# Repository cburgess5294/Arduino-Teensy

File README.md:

# Arduino-Teensy
Repository for files related to the Arduino-Teensy v4

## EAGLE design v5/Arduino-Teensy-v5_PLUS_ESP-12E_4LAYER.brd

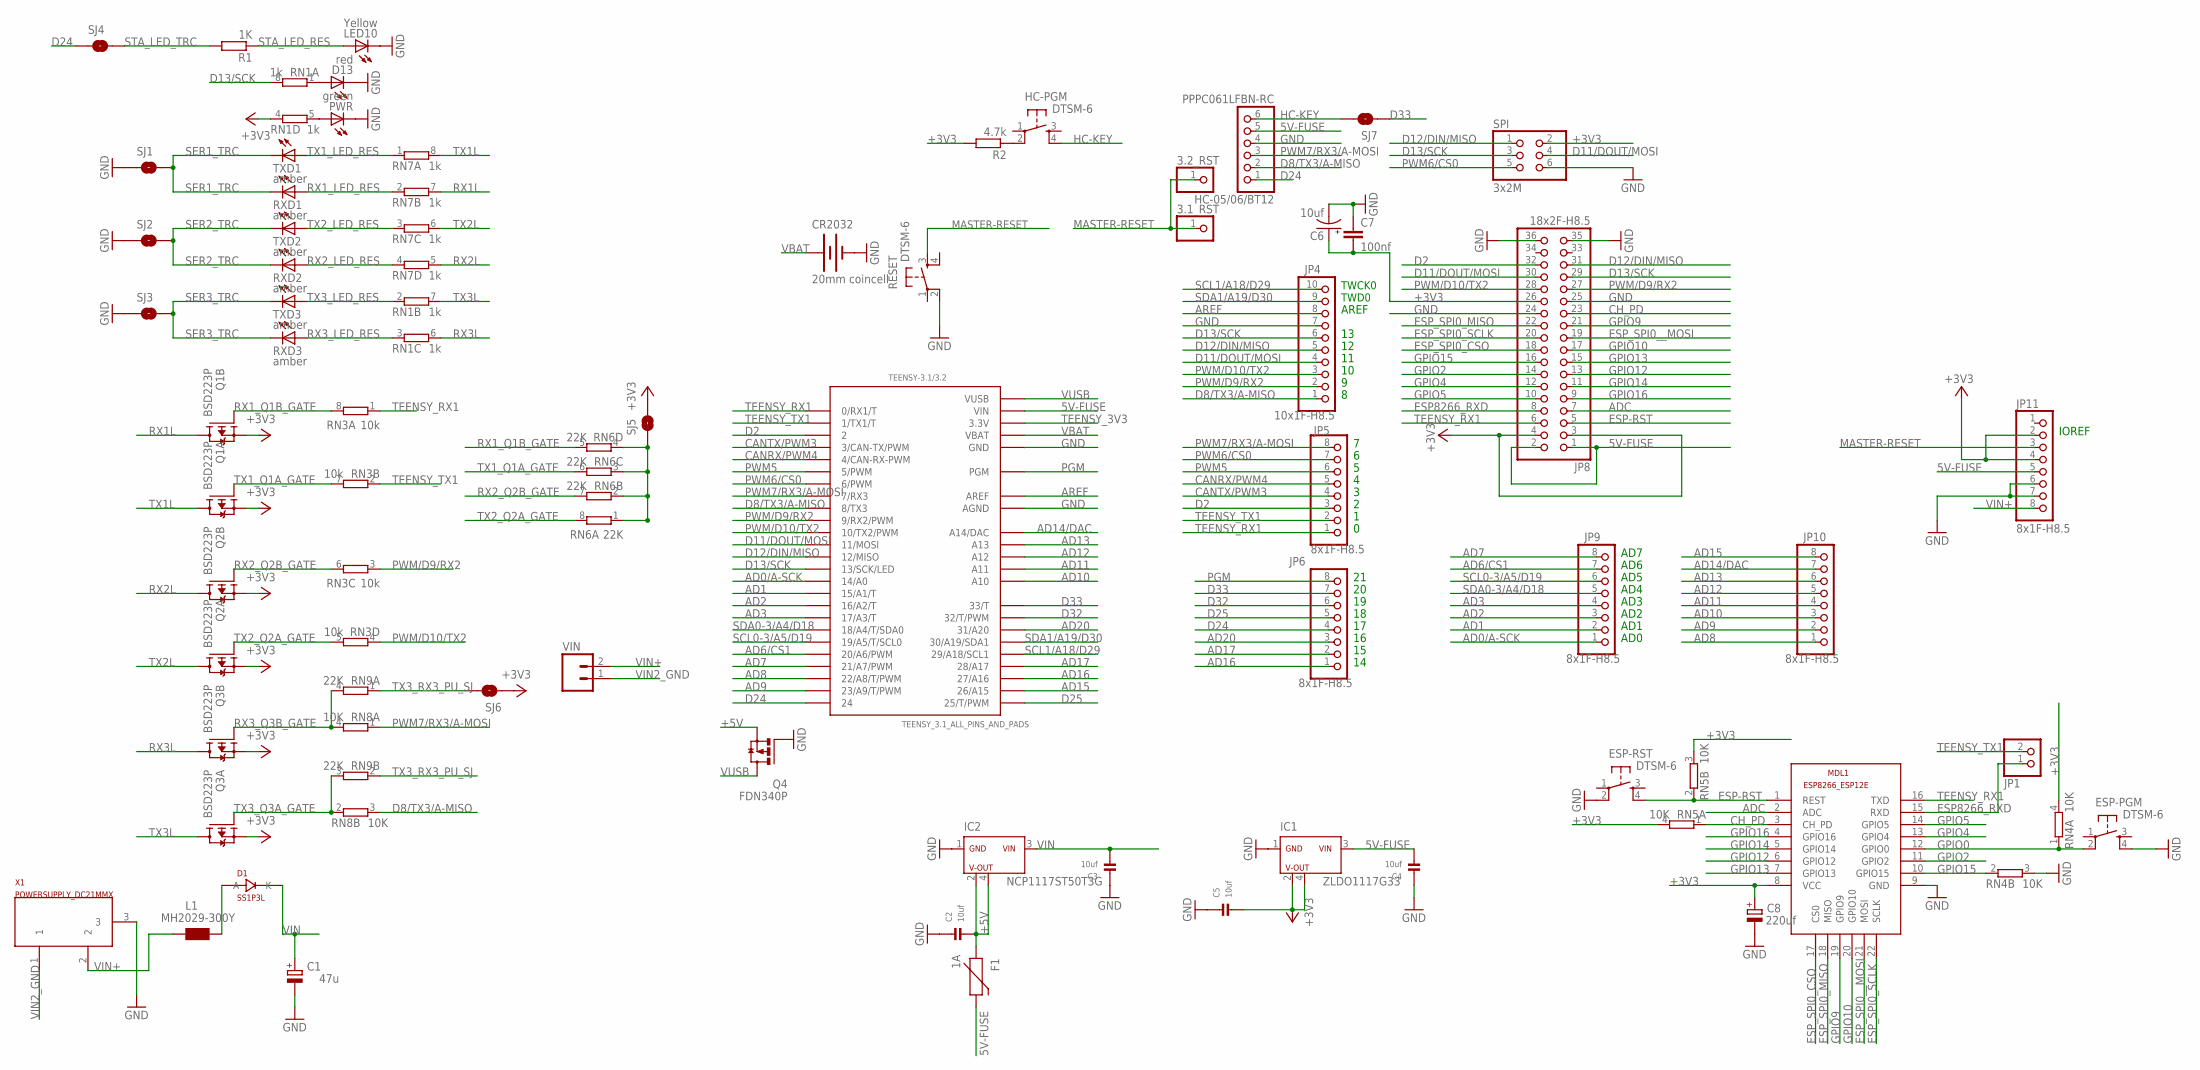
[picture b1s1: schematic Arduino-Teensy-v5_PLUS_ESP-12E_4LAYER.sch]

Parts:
3.1_RST, 3.2_RST: PINHD-1X1CB; 1X01-CLEANBIG
C1: 47u; PANASONIC_D
C2, C3, C4, C5: 10uf; 0805
C6: 10uf; A/3216-18R
C7: 100nf; C0603-ROUND
C8: 220uf; SMC_B
CR2032: 20mm coincell; BATTCON_20MM_4LEGS
D1: SS1P3L; DO220AAL
D13: red; CHIPLED_0805
ESP-PGM: DTSM-6
ESP-RST: DTSM-6
F1: 1A; PTC-1206
HC-05/06/BT12: PPPC061LFBN-RC; 1X06
HC-PGM: DTSM-6
IC1: ZLDO1117G33; SOT223
IC2: NCP1117ST50T3G; SOT223
JP1: PINHD-1X2; 1X02
JP4: 10x1F-H8.5; 1X10
JP5, JP6, JP9, JP10, JP11: 8x1F-H8.5; 1X08
JP8: 18x2F-H8.5; 2X18
L1: MH2029-300Y; 0805
LED10: Yellow; CHIPLED_0805
MDL1: ESP8266-12E); ESP8266-ESP12E
PWR: green; CHIPLED_0805
Q1, Q2, Q3: BSD223P; SOT363_INFINEON
Q4: FDN340P; SUPER-SOT3
R1: 1K; R0603
R2: 4.7k; R0603
RESET: DTSM-6
RN1, RN7: 1k; CAT16
RN3: 10k; CAT16
RN4, RN5, RN8: 10K; EXB34V
RN6: 22K; CAT16
RN9: 22K; EXB34V
RXD1, RXD2, RXD3: amber; CHIPLED_0805
SJ1, SJ2, SJ3, SJ4, SJ5, SJ6, SJ7: SOLDERJUMPERTRACE; SJ_2S-TRACE
SPI: 3x2M; 2X03
TEENSY-3.1/3.2: TEENSY_3.1_ALL_PINS_AND_PADS; TEENSY3_ALL_PINS_&_PADS
TXD1, TXD2, TXD3: amber; CHIPLED_0805
VIN: M02LOCK_LONGPADS; 1X02_LOCK_LONGPADS
X1: POWERSUPPLY_DC21MMX; POWERSUPPLY_DC-21MM

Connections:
5V-FUSE: C4.2, F1.2, HC-05/06/BT12.5, IC1.3 (VIN), JP8.1, JP8.2, JP11.5, TEENSY-3.1/3.2.VIN
+3V3: C5.2, C6.+, C7.2, C8.+, IC1.2 (VOUT), IC1.4 (VOUT), JP8.3, JP8.4, JP8.26, JP11.2, JP11.4, MDL1.8 (VCC), Q1.1 (S), Q1.4 (S), Q2.1 (S), Q2.4 (S), Q3.1 (S), Q3.4 (S), R2.2, RN1.4 (1), RN4.4 (2), RN5.3 (2), RN5.4 (2), SJ5.2, SJ6.1, SPI.2
+5V: C2.2, F1.1, IC2.2 (VOUT), IC2.4 (VOUT), Q4.2 (S)
AD0/A-SCK: JP9.1, TEENSY-3.1/3.2.14/A0
AD1: JP9.2, TEENSY-3.1/3.2.15/A1 (15/A1/T)
AD2: JP9.3, TEENSY-3.1/3.2.16/A2 (16/A2/T)
AD3: JP9.4, TEENSY-3.1/3.2.17/A3 (17/A3/T)
AD6/CS1: JP9.7, TEENSY-3.1/3.2.20/A6 (20/A6/PWM)
AD7: JP9.8, TEENSY-3.1/3.2.21/A7 (21/A7/PWM)
AD8: JP10.1, TEENSY-3.1/3.2.22/A8 (22/A8/T/PWM)
AD9: JP10.2, TEENSY-3.1/3.2.23/A9 (23/A9/T/PWM)
AD10: JP10.3, TEENSY-3.1/3.2.A10
AD11: JP10.4, TEENSY-3.1/3.2.A11
AD12: JP10.5, TEENSY-3.1/3.2.A12
AD13: JP10.6, TEENSY-3.1/3.2.A13
AD14/DAC: JP10.7, TEENSY-3.1/3.2.RESET/DAC (A14/DAC)
AD15: JP10.8, TEENSY-3.1/3.2.26 (26/A15)
AD16: JP6.1, TEENSY-3.1/3.2.27 (27/A16)
AD17: JP6.2, TEENSY-3.1/3.2.28 (28/A17)
AD20: JP6.3, TEENSY-3.1/3.2.31 (31/A20)
ADC: JP8.7, MDL1.2 (ADC)
AREF: JP4.8, TEENSY-3.1/3.2.AREF
CANRX/PWM4: JP5.5, TEENSY-3.1/3.2.4 (4/CAN-RX-PWM)
CANTX/PWM3: JP5.4, TEENSY-3.1/3.2.3 (3/CAN-TX/PWM)
CH_PD: JP8.23, MDL1.3 (CH_PD), RN5.1
D2: JP5.3, JP8.32, TEENSY-3.1/3.2.2
D8/TX3/A-MISO: HC-05/06/BT12.2, JP4.1, RN8.3 (2), TEENSY-3.1/3.2.8 (8/TX3)
D11/DOUT/MOSI: JP4.4, JP8.30, SPI.4, TEENSY-3.1/3.2.11 (11/MOSI)
D12/DIN/MISO: JP4.5, JP8.31, SPI.1, TEENSY-3.1/3.2.12 (12/MISO)
D13/SCK: JP4.6, JP8.29, RN1.8 (2), SPI.3, TEENSY-3.1/3.2.13 (13/SCK/LED)
D24: HC-05/06/BT12.1, JP6.4, SJ4.1, TEENSY-3.1/3.2.24
D25: JP6.5, TEENSY-3.1/3.2.25 (25/T/PWM)
D32: JP6.6, TEENSY-3.1/3.2.32 (32/T/PWM)
D33: JP6.7, SJ7.2, TEENSY-3.1/3.2.33 (33/T)
ESP8266_RXD: JP1.1, JP8.8, MDL1.15 (RXD)
ESP-RST: ESP-RST.4, JP8.5, MDL1.1 (REST), RN5.2 (1)
ESP_SPI0_CSO: JP8.18, MDL1.17 (CS0)
ESP_SPI0_MISO: JP8.22, MDL1.18 (MISO)
ESP_SPI0_SCLK: JP8.20, MDL1.22 (SCLK)
ESP_SPI0__MOSI: JP8.19, MDL1.21 (MOSI)
GND: C1.-, C2.1, C3.1, C4.1, C5.1, C6.-, C7.1, C8.-, CR2032.NEGATIVE (-), D13.C, ESP-PGM.4, ESP-RST.2, HC-05/06/BT12.4, IC1.1 (GND), IC2.1 (GND), JP4.7, JP8.24, JP8.25, JP8.35, JP8.36, JP11.6, JP11.7, LED10.C, MDL1.9 (GND), PWR.C, Q4.1 (G), RESET.2, RN4.3 (2), SJ1.1, SJ2.1, SJ3.1, SPI.6, TEENSY-3.1/3.2.AGND, TEENSY-3.1/3.2.GND, TEENSY-3.1/3.2.GND1 (GND), TEENSY-3.1/3.2.GND2 (GND), X1.3
GPIO0: ESP-PGM.2, MDL1.12 (GPIO0), RN4.1
GPIO2: JP8.14, MDL1.11 (GPIO2)
GPIO4: JP8.12, MDL1.13 (GPIO4)
GPIO5: JP8.10, MDL1.14 (GPIO5)
GPIO9: JP8.21, MDL1.19 (GPIO9)
GPIO10: JP8.17, MDL1.20 (GPIO10)
GPIO12: JP8.13, MDL1.6 (GPIO12)
GPIO13: JP8.15, MDL1.7 (GPIO13)
GPIO14: JP8.11, MDL1.5 (GPIO14)
GPIO15: JP8.16, MDL1.10 (GPIO15), RN4.2 (1)
GPIO16: JP8.9, MDL1.4 (GPIO16)
HC-KEY: HC-05/06/BT12.6, HC-PGM.4, SJ7.1
MASTER-RESET: 3.1_RST.1, 3.2_RST.1, JP11.3, RESET.3
unnamed: PWR.A, RN1.5 (2)
unnamed: D13.A, RN1.1
unnamed: HC-PGM.2, R2.1
PGM: JP6.8, TEENSY-3.1/3.2.PGM
PWM5: JP5.6, TEENSY-3.1/3.2.5 (5/PWM)
PWM6/CS0: JP5.7, SPI.5, TEENSY-3.1/3.2.6 (6/PWM)
PWM7/RX3/A-MOSI: HC-05/06/BT12.3, JP5.8, RN8.1, TEENSY-3.1/3.2.7 (7/RX3)
PWM/D9/RX2: JP4.2, JP8.27, RN3.3 (1), TEENSY-3.1/3.2.9 (9/RX2/PWM)
PWM/D10/TX2: JP4.3, JP8.28, RN3.4 (1), TEENSY-3.1/3.2.10 (10/TX2/PWM)
RX1L: Q1.3 (D), RN7.7 (2)
RX1_LED_RES: RN7.2 (1), RXD1.A
RX1_Q1B_GATE: Q1.5 (G), RN3.8 (2), RN6.5 (2)
RX1_TX1_RX2_TX2_PU_SJ: RN6.1, RN6.2 (1), RN6.3 (1), RN6.4 (1), SJ5.1
RX2L: Q2.3 (D), RN7.5 (2)
RX2_LED_RES: RN7.4 (1), RXD2.A
RX2_Q2B_GATE: Q2.5 (G), RN3.6 (2), RN6.7 (2)
RX3L: Q3.3 (D), RN1.6 (2)
RX3_LED_RES: RN1.3 (1), RXD3.A
RX3_Q3B_GATE: Q3.5 (G), RN8.4 (2), RN9.4 (2)
SCL0-3/A5/D19: JP9.6, TEENSY-3.1/3.2.19/A5 (19/A5/T/SCL0)
SCL1/A18/D29: JP4.10, TEENSY-3.1/3.2.29 (29/A18/SCL1)
SDA0-3/A4/D18: JP9.5, TEENSY-3.1/3.2.18/A4 (18/A4/T/SDA0)
SDA1/A19/D30: JP4.9, TEENSY-3.1/3.2.30 (30/A19/SDA1)
SER1_TRC: RXD1.C, SJ1.2, TXD1.C
SER2_TRC: RXD2.C, SJ2.2, TXD2.C
SER3_TRC: RXD3.C, SJ3.2, TXD3.C
STA_LED_RES: LED10.A, R1.1
STA_LED_TRC: R1.2, SJ4.2
TEENSY_3V3: TEENSY-3.1/3.2.3.3V, TEENSY-3.1/3.2.3.3V1 (3.3V), TEENSY-3.1/3.2.3.3V2 (3.3V)
TEENSY_RX1: JP5.1, JP8.6, MDL1.16 (TXD), RN3.1, TEENSY-3.1/3.2.0 (0/RX1/T)
TEENSY_TX1: JP1.2, JP5.2, RN3.2 (1), TEENSY-3.1/3.2.1 (1/TX1/T)
TX1L: Q1.6 (D), RN7.8 (2)
TX1_LED_RES: RN7.1, TXD1.A
TX1_Q1A_GATE: Q1.2 (G), RN3.7 (2), RN6.6 (2)
TX2L: Q2.6 (D), RN7.6 (2)
TX2_LED_RES: RN7.3 (1), TXD2.A
TX2_Q2A_GATE: Q2.2 (G), RN3.5 (2), RN6.8 (2)
TX3L: Q3.6 (D), RN1.7 (2)
TX3_LED_RES: RN1.2 (1), TXD3.A
TX3_Q3A_GATE: Q3.2 (G), RN8.2 (1), RN9.3 (2)
TX3_RX3_PU_SJ: RN9.1, RN9.2 (1), SJ6.2
VBAT: CR2032.POSITIVE@1 (+), CR2032.POSITIVE@2 (+), CR2032.POSITIVE@3 (+), CR2032.POSITIVE@4 (+), TEENSY-3.1/3.2.VBAT
VIN: C1.+, C3.2, D1.P$1 (K), IC2.3 (VIN)
VIN2_GND: VIN.1, X1.1
VIN+: JP11.8, L1.2, VIN.2, X1.2
VIN_FER_DIO: D1.P$2 (A), L1.1
VUSB: Q4.3 (D), TEENSY-3.1/3.2.VUSB

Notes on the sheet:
IOREF
TWCK0
TWD0
AD1
AD2
AD3
AD4
AD5
AD6
AD0
AREF
AD7

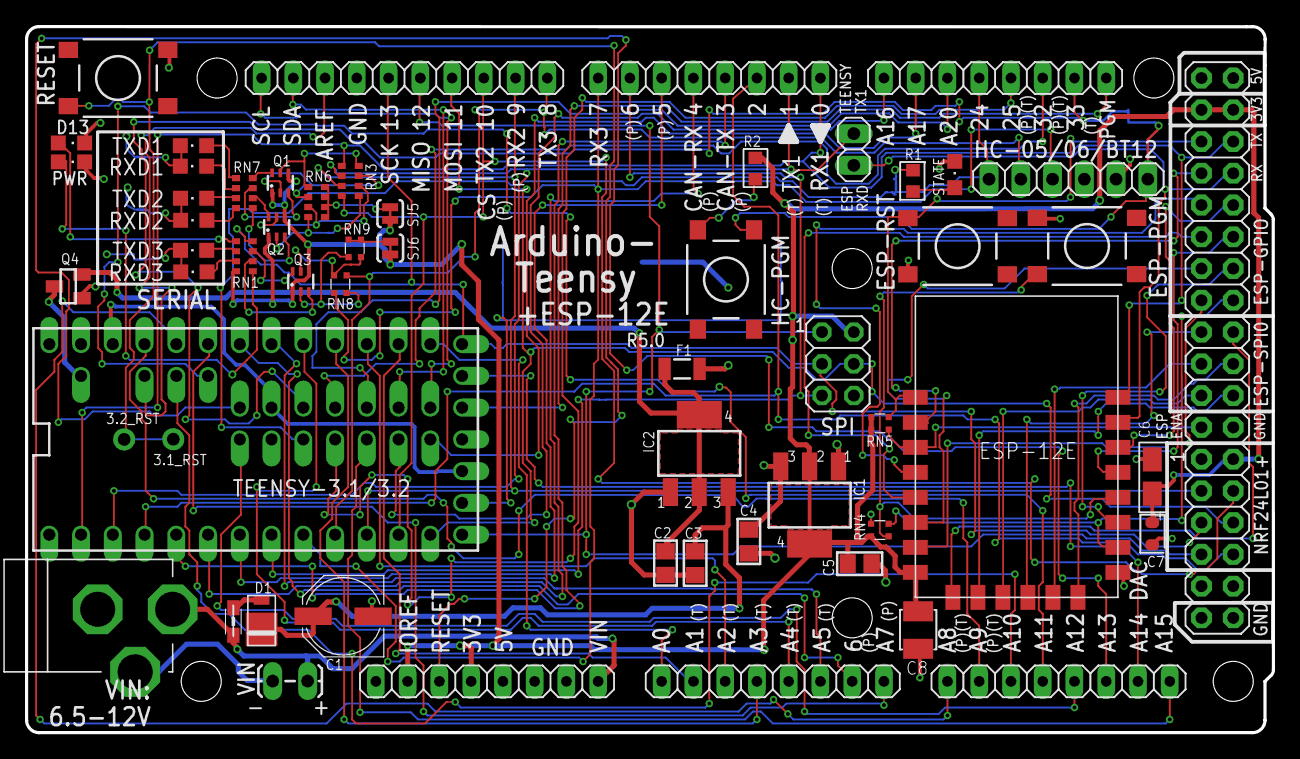
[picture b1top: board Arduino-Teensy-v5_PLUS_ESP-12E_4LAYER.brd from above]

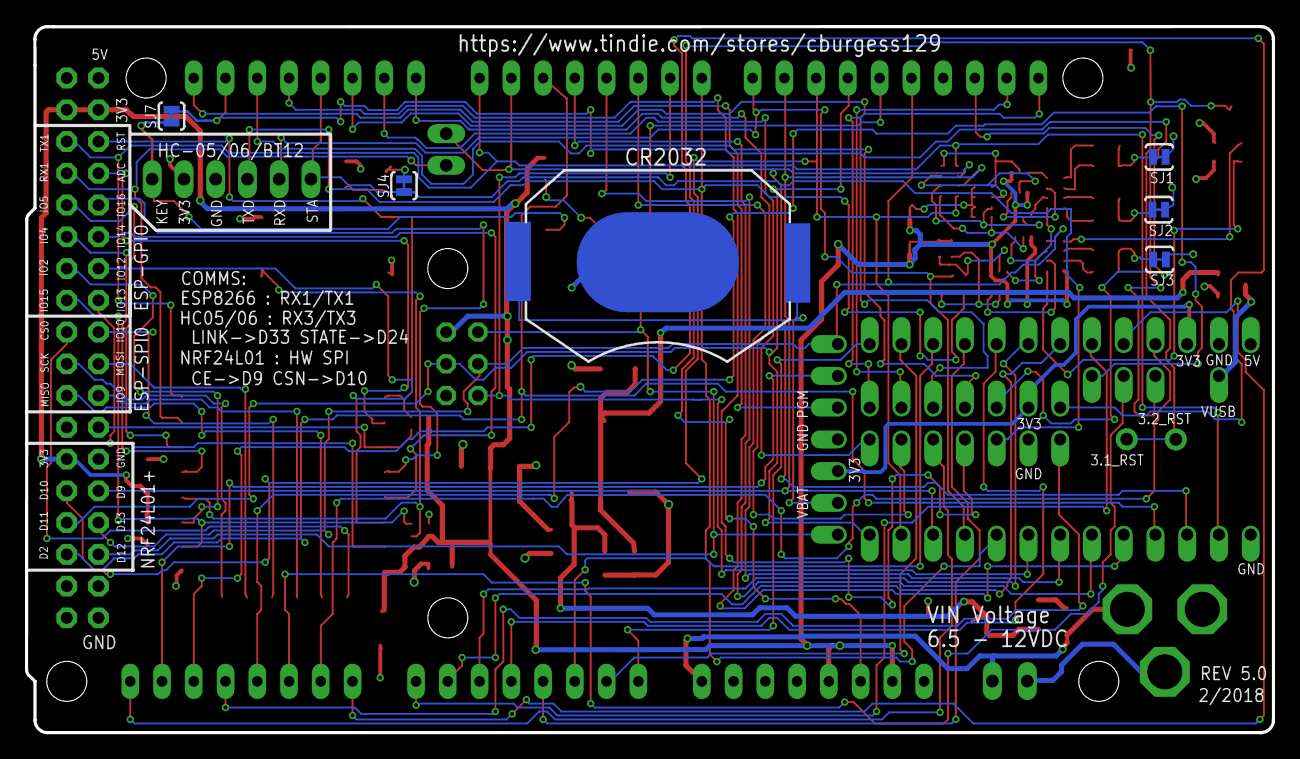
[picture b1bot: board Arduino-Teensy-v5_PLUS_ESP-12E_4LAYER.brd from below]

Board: 4 copper layers, 99.7 x 56.5 mm, 64 parts (6 on the bottom side), 101 nets.

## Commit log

2017-09-20 Create temp
2019-01-10 add arduino-teensy test script
2019-01-10 Rename ArduinoTeensy_Test_Sketch_v1 to ArduinoTeensy_Test_Sketch_v1.ino

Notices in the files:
parts and their libraries:
SparkFun-Electromechanical: Licensing: Creative Commons ShareAlike 4.0 International - https://creativecommons.org/licenses/by-sa/4.0
